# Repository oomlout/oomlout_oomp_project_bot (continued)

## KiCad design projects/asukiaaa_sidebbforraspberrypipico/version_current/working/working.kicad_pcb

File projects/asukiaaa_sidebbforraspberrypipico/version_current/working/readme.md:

# OOMP Project  
## SideBBForRaspberryPiPico  by asukiaaa  
  
oomp key: oomp_projects_flat_asukiaaa_sidebbforraspberrypipico  
(snippet of original readme)  
  
- SideBBForRaspberryPiPico  
  
A KiCad PCB project for raspberry pi pico.  

-- Where to buy  
  
[SideBB For Raspberry Pi Pico - switch science](https://ssci.to/8837)  
  
-- References  
  
- [Raspberry Pi Pico datasheet (PDF)](https://datasheets.raspberrypi.com/pico/pico-datasheet.pdf)  
  
  full source readme at [readme_src.md](readme_src.md)  
  
source repo at: [https://github.com/asukiaaa/SideBBForRaspberryPiPico](https://github.com/asukiaaa/SideBBForRaspberryPiPico)  
## Board  

## Schematic  

[schematic pdf](working_schematic.pdf)  
## Images

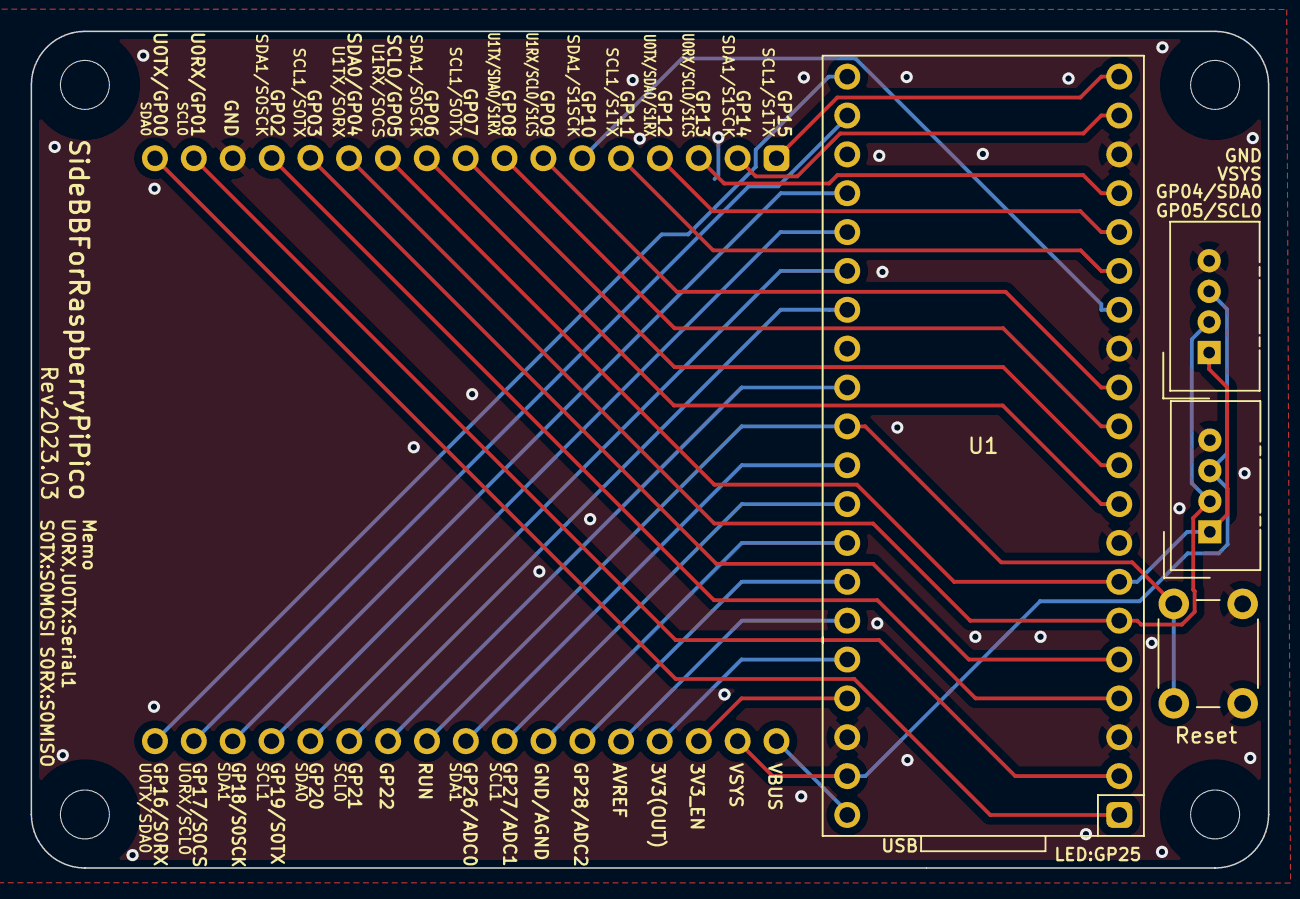
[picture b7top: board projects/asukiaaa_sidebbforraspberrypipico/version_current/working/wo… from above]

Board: 2 copper layers, 80.9 x 54.7 mm, 9 parts (0 on the bottom side), 34 nets.

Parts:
J1: mini-bread-board-1x17x2
J2, J3: Grove-I2C-connector; NS-Tech_Grove_1x04_P2mm_Vertical
REF1, REF2, REF3, REF4: MountingHole_3.2mm_M3_bare
SW1: SW_Push; SW_PUSH_6mm
U1: Pico; RPi_Pico_TH

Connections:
+3V3: J1.31, U1.36 (3V3)
/3V3_EN: J1.32, U1.37 (3V3_EN)
/AGND: J1.28, U1.33 (AGND)
/AVREF: J1.30, U1.35 (ADC_VREF)
/GPI18: J1.20, U1.24 (GPIO18)
/GPIO0: J1.17 (Pin_34), U1.1 (GPIO0)
/GPIO1: J1.16 (Pin_33), U1.2 (GPIO1)
/GPIO2: J1.14 (Pin_31), U1.4 (GPIO2)
/GPIO3: J1.13 (Pin_30), U1.5 (GPIO3)
/GPIO4: J1.12 (Pin_29), J2.2 (SDA), J3.2 (SDA), U1.6 (GPIO4)
/GPIO5: J1.11 (Pin_28), J2.1 (SCL), J3.1 (SCL), U1.7 (GPIO5)
/GPIO6: J1.10 (Pin_27), U1.9 (GPIO6)
/GPIO7: J1.9 (Pin_26), U1.10 (GPIO7)
/GPIO8: J1.8 (Pin_25), U1.11 (GPIO8)
/GPIO9: J1.7 (Pin_24), U1.12 (GPIO9)
/GPIO10: J1.6 (Pin_23), U1.14 (GPIO10)
/GPIO11: J1.5 (Pin_22), U1.15 (GPIO11)
/GPIO12: J1.4 (Pin_21), U1.16 (GPIO12)
/GPIO13: J1.3 (Pin_20), U1.17 (GPIO13)
/GPIO14: J1.2 (Pin_19), U1.19 (GPIO14)
/GPIO15: J1.1 (Pin_18), U1.20 (GPIO15)
/GPIO16: J1.18, U1.21 (GPIO16)
/GPIO17: J1.19, U1.22 (GPIO17)
/GPIO19: J1.21, U1.25 (GPIO19)
/GPIO20: J1.22, U1.26 (GPIO20)
/GPIO21: J1.23, U1.27 (GPIO21)
/GPIO22: J1.24, U1.29 (GPIO22)
/GPIO26: J1.26, U1.31 (GPIO26_ADC0)
/GPIO27: J1.27, U1.32 (GPIO27_ADC1)
/GPIO28: J1.29, U1.34 (GPIO28_ADC2)
/RUN: J1.25, SW1.1, U1.30 (RUN)
/VBUS: J1.34, U1.40 (VBUS)
/VSYS: J1.33, J2.3 (VCC), J3.3 (VCC), U1.39 (VSYS)
GND: J1.15 (Pin_32), J2.4 (GND), J3.4 (GND), SW1.2, U1.3 (GND), U1.8 (GND), U1.13 (GND), U1.18 (GND), U1.23 (GND), U1.28 (GND), U1.38 (GND)

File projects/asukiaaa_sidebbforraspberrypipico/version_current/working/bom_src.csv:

Ref,Qnty,Value,Cmp name,Footprint,Description,url,memo
"J1, ",1,mini-bread-board-1x17x2,mini-bread-board-1x17x2,asukiaaa-kicad-footprints:mini-bread-board-1x17x2,17x1 pin socket white x2,,
"J2, J3, ",2,Grove-I2C-connector,Grove-I2C-connector,Connector:NS-Tech_Grove_1x04_P2mm_Vertical,Grove vertical socket,https://www.seeedstudio.com/Grove-Universal-4-pin-connector.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,I don’t mind vendor
"SW1, ",1,SW_Push,SW_Push,Button_Switch_THT:SW_PUSH_6mm,white,,
"U1, ",1,Pico,Pico,asukiaaa-kicad-footprints:RPi_Pico_TH,20x1 pin socket white x2,,
,4,,,,M3 5mm Spacer,https://ja.aliexpress.com/item/100pcs-M3-Nylon-Hexagonal-Pil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,Include to baggage with the PCB. I don't mind vendor.
,4,,,,M3 Nut,https://ja.aliexpress.com/item/100pcs-M3-Nylon-Hexagonal-Pil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,Include to baggage with the PCB. I don't mind vendor.
